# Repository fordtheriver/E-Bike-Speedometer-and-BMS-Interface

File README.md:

# E-Bike-Speedometer-and-BMS-Interface

**Updated 7/25/19** Completed, manufactured, and test REV4 of board. It works! REV3 is also complete.

This repository includes information needed to built a display to output the speed, mileage, power, current, pack voltage, individual cell voltage abd State of Charge of an electric bicycle/powerwall using an Arduino Nano! This repository includes the necessary Arduino files, a custom Arduino shield PCB designed in EAGLE and various information about the components required to build this system.

There are two versions of this system which you can build: <br /> 
**REV3:** This is a simple board that requires little soldering or PCB design experience. Beginners start here! <br /> 
**REV4:** This board is identical to REV3 but it embedds the arduino nano onto the board, instead of through-hole mounting a off-the-shelf arduino nano. <br /> 
Both REV's function identically. Think of REV3 as a demo board where you can develop firmware and prototype the system. REV4 gets into the low level side and allows for greater custimizations and smaller size.

Here is a brief list describing the necessary high level components for this system.

1. Arduino Nano. REV4 embeds the ATmega328P micrcoprocessor on the board to significantly reduce system size and weight. 

2. [20x4 LCD Display with I2C.](https://www.ebay.com/sch/i.html?_from=R40&_trksid=m570.l1313&_nkw=20x4+i2c+lcd+&_sacat=0). The I2C communication bus drastically reduces the number of wires going to the LCD and the \#include <LiquidCrystal_I2C.h> library seamlessly integrates the I2C protocol into your arduino. 

3. JBDTools Compatible BMS: Here is a [link](https://www.aliexpress.com/item/15S-Li-ion-Battery-Intelligent-Smart-BMS-with-Bluetooth-function-and-PC-software-UART-communication-PCB/32876909159.html?spm=a2g0s.13010208.99999999.263.70483c00UKdgf7) to the one I purchased.  . Make sure the BMS you buy is compatible with JBDTools software. My arduino script uses the communication protocol used by the JBDTools software. This protocol can be found in an excel file call JBDTools Communication Protol at the homepage of this repository. [Simat](https://github.com/simat/BatteryMonitor/wiki/Generic-Chinese-Bluetooth-BMS-communication-protocol) also has a great description of it as well. 

4. DC/DC Converter. The linear voltage regulator on [this](https://www.aliexpress.com/item/15S-Li-ion-Battery-Intelligent-Smart-BMS-with-Bluetooth-function-and-PC-software-UART-communication-PCB/32876909159.html?spm=a2g0s.13010208.99999999.263.70483c00UKdgf7) type of BMS is not designed to handle high amounts of current. REV3 of this project includes [this](https://www.mouser.com/ProductDetail/MEAN-WELL/SKM15C-12?qs=erfQA2AIGbWiXI5iTXq5SA%3D%3D) or [this](https://www.mouser.com/ProductDetail/Cincon/EC4SBW-48S12?qs=sGAEpiMZZMvGsmoEFRKS8Koqt8Pjkl39iYdgR2DcyS1Q8fqJi%252BFKOA%3D%3D) DC/DC converter to provide 12V at a max of 1.25A to the system.

5. [Hall effect sensor.](https://www.adafruit.com/product/158). This type of sensor send a HIGH pulse whenever a significant magnetic field acts upon it.

6. Connectors. [Housing](https://www.mouser.com/ProductDetail/Molex/70543-0001?qs=sGAEpiMZZMtVoztFdqDXOwZ%252B3K3gi96X). [Plug](https://www.mouser.com/ProductDetail/Molex/50-57-9402?qs=%2Fha2pyFaduiLH0020kLaRTyvVPMd9o3wI7LfZqK7vYk%3D). [Crimp Pin](https://www.mouser.com/ProductDetail/Molex/16-02-0086-Cut-Strip?qs=sGAEpiMZZMs%252BGHln7q6pm%252Bv5BXf4QdrTI%252BpAylNNmmH%2F60rOt1UzkQ%3D%3D)

7. EAGLE PCB design software. I used [OSHPark](https://oshpark.com/) to manufacture the PCB and had no issues. 

# High Level System Requirements:

1. Input Voltage Range: 18 - 72 Volts
2. Max Power Output at 12V: 1.67 Amps (20W)
3. Reverse polarity and fuse protection on power input

# Good Tips:

My ebike uses the Cyclone 3000 ebike kit. The throttle/ignition has a built in switch on the B+ line. My system draws power from the B+ after this switch so that if the switch opens, the system turns off. I recommend configuring your system this way so that it only draws power when the bike is on.

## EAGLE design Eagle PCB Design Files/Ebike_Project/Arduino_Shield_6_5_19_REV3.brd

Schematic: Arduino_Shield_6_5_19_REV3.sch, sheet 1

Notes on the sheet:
Connector Housing Series 70543 - Part No: 705430004 (4 PIN)
Connector Plug Series 70066 - Part No: 505794XX
Connector Crimp Series 70058 - Part No: 16020086
Wire to Wire Housing Crimp: 70021-1021
Wire to Wire Housing Series: 70107 - Part No: 701070003
BMS_SWITCH
IGNITION_SWITCH

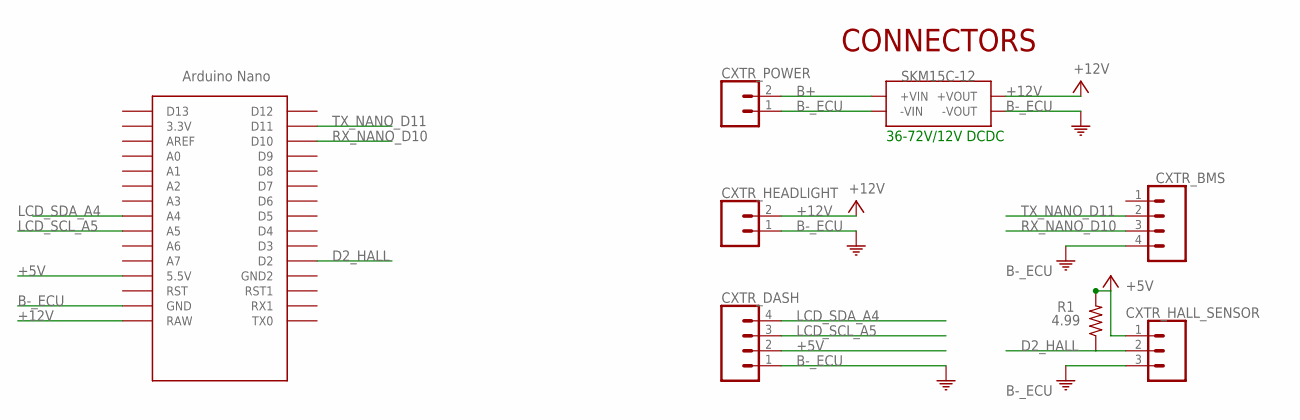
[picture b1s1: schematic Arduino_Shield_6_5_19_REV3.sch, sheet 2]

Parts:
CXTR_BMS: 4PIN_.1"_CONNECTOR; 1X04
CXTR_DASH: 4PIN_.1"_CONNECTOR; 1X04
CXTR_HALL_SENSOR: 3PIN_.1"_CONNECTOR; 1X03
CXTR_HEADLIGHT: 2PIN_.1"_CONNECTOR; 1X02
CXTR_POWER: 2PIN_.1"_CONNECTOR; 1X02
R1: 4.99; 0805
U$2: SKM15C-12_DCDC
U$3: ARDUINO_NANO; NANO

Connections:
+5V: CXTR_DASH.2, CXTR_HALL_SENSOR.1, R1.2, U$3.5V (5.5V)
+12V: CXTR_HEADLIGHT.2, U$2.+VOUT, U$3.RAW
B+: CXTR_POWER.2, U$2.+VIN
B-_ECU: CXTR_BMS.4, CXTR_DASH.1, CXTR_HALL_SENSOR.3, CXTR_HEADLIGHT.1, CXTR_POWER.1, U$2.-VIN, U$2.-VOUT, U$3.GND
D2_HALL: CXTR_HALL_SENSOR.2, R1.1, U$3.D2
LCD_SCL_A5: CXTR_DASH.3, U$3.A5
LCD_SDA_A4: CXTR_DASH.4, U$3.A4
RX_NANO_D10: CXTR_BMS.3, U$3.D10
TX_NANO_D11: CXTR_BMS.2, U$3.D11

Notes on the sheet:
36-72V/12V DCDC
CONNECTORS

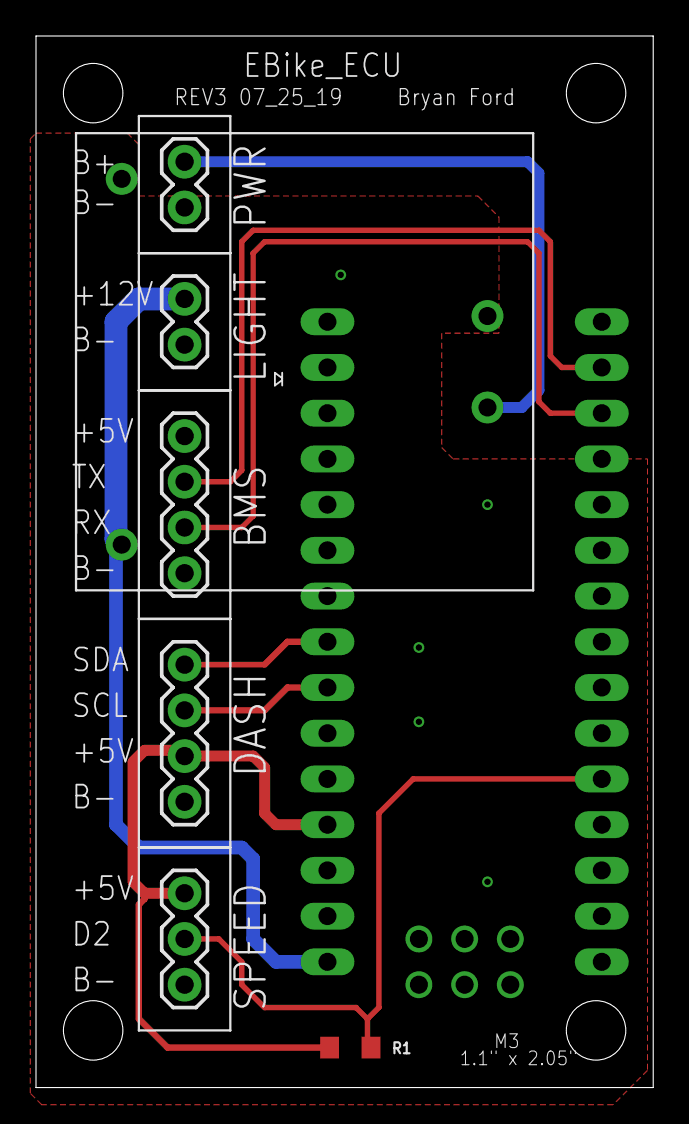
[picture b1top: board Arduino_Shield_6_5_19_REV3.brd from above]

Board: 2 copper layers, 34.3 x 58.4 mm, 8 parts (0 on the bottom side), 9 nets.

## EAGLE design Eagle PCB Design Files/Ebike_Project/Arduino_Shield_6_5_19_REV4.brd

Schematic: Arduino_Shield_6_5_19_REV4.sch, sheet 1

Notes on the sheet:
Connector Housing Series 70543 - Part No: 705430004 (4 PIN)
Connector Plug Series 70066 - Part No: 505794XX
Connector Crimp Series 70058 - Part No: 16020086
Wire to Wire Housing Crimp: 70021-1021
Wire to Wire Housing Series: 70107 - Part No: 701070003
BMS_SWITCH
IGNITION_SWITCH

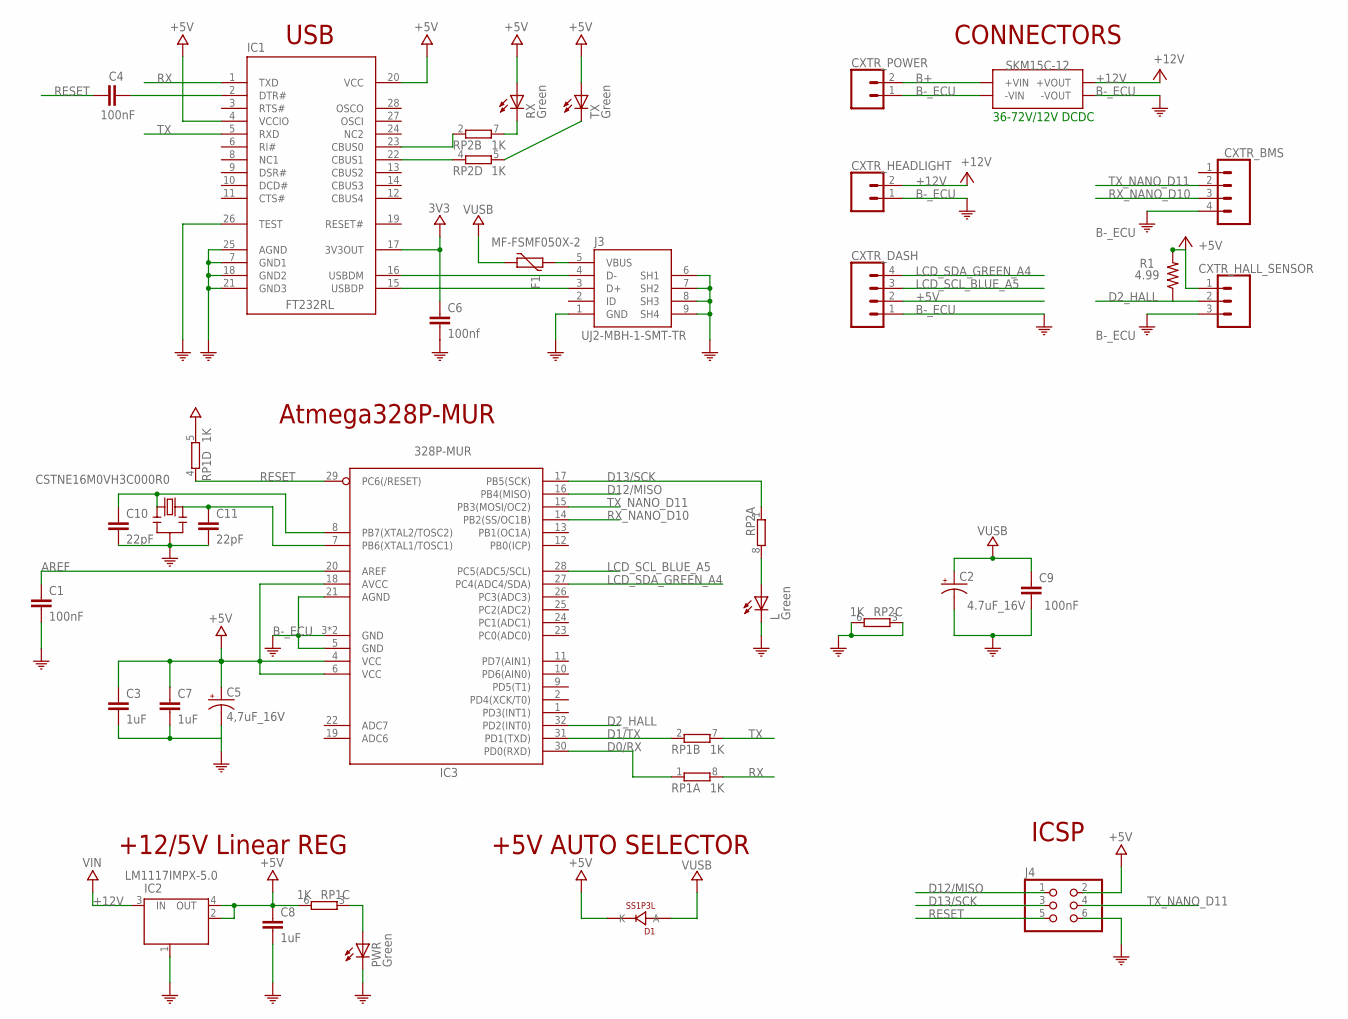
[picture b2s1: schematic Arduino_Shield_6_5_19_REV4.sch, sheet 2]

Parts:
C1, C4, C9: 100nF; 0805
C2: 4.7uF_16V; 0805
C3, C7, C8: 1uF; 0805
C5: 4,7uF_16V; 0805
C6: 100nf; 0805
C10, C11: 22pF; 0805
CXTR_BMS: 4PIN_.1"_CONNECTOR; 1X04
CXTR_DASH: 4PIN_.1"_CONNECTOR; 1X04
CXTR_HALL_SENSOR: 3PIN_.1"_CONNECTOR; 1X03
CXTR_HEADLIGHT: 2PIN_.1"_CONNECTOR; 1X02
CXTR_POWER: 2PIN_.1"_CONNECTOR; 1X02
D1: SS1P3L; SCHOTTKY_DIODE_DO220AAL
F1: MF-FSMF050X-2; 0603
IC1: FT232RL; USB_SSOP28
IC2: LM1117IMPX-5.0; LINEAR_VREG_SOT223
IC3: 328P-MUR; VQFN32
J3: UJ2-MBH-1-SMT-TR; USB-MINI-B_2
J4: 2X3_.1"_ARRAY; 2X03
L: Green; LED_0805
PWR: Green; LED_0805
R1: 4.99; 0805
RESONATOR: CSTNE16M0VH3C000R0; CRISTALLI_RESONATOR
RP1, RP2: 1K; RESISTOR_ARRAY_CAY16
RX: Green; LED_0805
TX: Green; LED_0805
U$2: SKM15C-12_DCDC

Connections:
3V3: C6.1, IC1.17 (3V3OUT)
+5V: C3.1, C5.1 (+), C7.1, C8.1, CXTR_DASH.2, CXTR_HALL_SENSOR.1, D1.P$1 (K), IC1.4 (VCCIO), IC1.20 (VCC), IC2.2 (OUT), IC2.4 (OUT), IC3.4 (VCC), IC3.6 (VCC), IC3.18 (AVCC), J4.2, R1.2, RP1.5 (2), RP1.6 (2), RX.A, TX.A
+12V: CXTR_HEADLIGHT.2, IC2.3 (IN), U$2.+VOUT
AREF: C1.1, IC3.20 (AREF)
B+: CXTR_POWER.2, U$2.+VIN
B-_ECU: C1.2, C2.2 (-), C3.2, C5.2 (-), C6.2, C7.2, C8.2, C9.2, C10.2, C11.2, CXTR_BMS.4, CXTR_DASH.1, CXTR_HALL_SENSOR.3, CXTR_HEADLIGHT.1, CXTR_POWER.1, IC1.7 (GND1), IC1.18 (GND2), IC1.21 (GND3), IC1.25 (AGND), IC1.26 (TEST), IC2.1 (GND/ADJ), IC3.3 (GND), IC3.5 (GND), IC3.21 (AGND), IC3.33 (GND), J3.1 (GND), J3.6 (SH1), J3.7 (SH2), J3.8 (SH3), J3.9 (SH4), J4.6, L.C, PWR.C, RESONATOR.2, RP2.3 (1), RP2.6 (2), U$2.-VIN, U$2.-VOUT
D0/RX: IC3.30 (PD0(RXD)), RP1.1
D1/TX: IC3.31 (PD1(TXD)), RP1.2 (1)
D2_HALL: CXTR_HALL_SENSOR.2, IC3.32 (PD2(INT0)), R1.1
D12/MISO: IC3.16 (PB4(MISO)), J4.1
D13/SCK: IC3.17 (PB5(SCK)), J4.3, RP2.1
LCD_SCL_BLUE_A5: CXTR_DASH.3, IC3.28 (PC5(ADC5/SCL))
LCD_SDA_GREEN_A4: CXTR_DASH.4, IC3.27 (PC4(ADC4/SDA))
unnamed: C4.2, IC1.2 (DTR#)
unnamed: IC1.15 (USBDP), J3.3 (D+)
unnamed: IC1.16 (USBDM), J3.4 (D-)
unnamed: PWR.A, RP1.3 (1)
unnamed: IC1.23 (CBUS0), RP2.2 (1)
unnamed: IC1.22 (CBUS1), RP2.4 (1)
unnamed: C11.1, IC3.7 (PB6(XTAL1/TOSC1)), RESONATOR.1
unnamed: L.A, RP2.8 (2)
unnamed: RP2.5 (2), TX.C
unnamed: C10.1, IC3.8 (PB7(XTAL2/TOSC2)), RESONATOR.3
unnamed: F1.2, J3.5 (VBUS)
unnamed: RP2.7 (2), RX.C
RESET: C4.1, IC3.29 (PC6(/RESET)), J4.5, RP1.4 (1)
RX: IC1.1 (TXD), RP1.8 (2)
RX_NANO_D10: CXTR_BMS.3, IC3.14 (PB2(SS/OC1B))
TX: IC1.5 (RXD), RP1.7 (2)
TX_NANO_D11: CXTR_BMS.2, IC3.15 (PB3(MOSI/OC2)), J4.4
VUSB: C2.1 (+), C9.1, D1.P$2 (A), F1.1

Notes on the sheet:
+12/5V Linear REG
ICSP
USB
+5V AUTO SELECTOR
36-72V/12V DCDC
Atmega328P-MUR
CONNECTORS

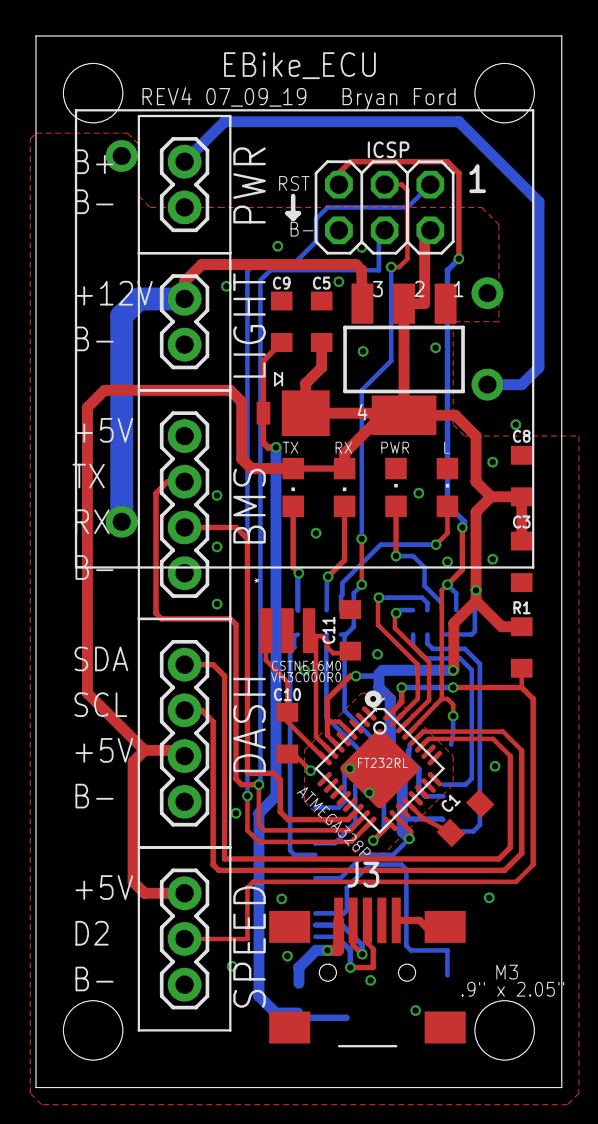
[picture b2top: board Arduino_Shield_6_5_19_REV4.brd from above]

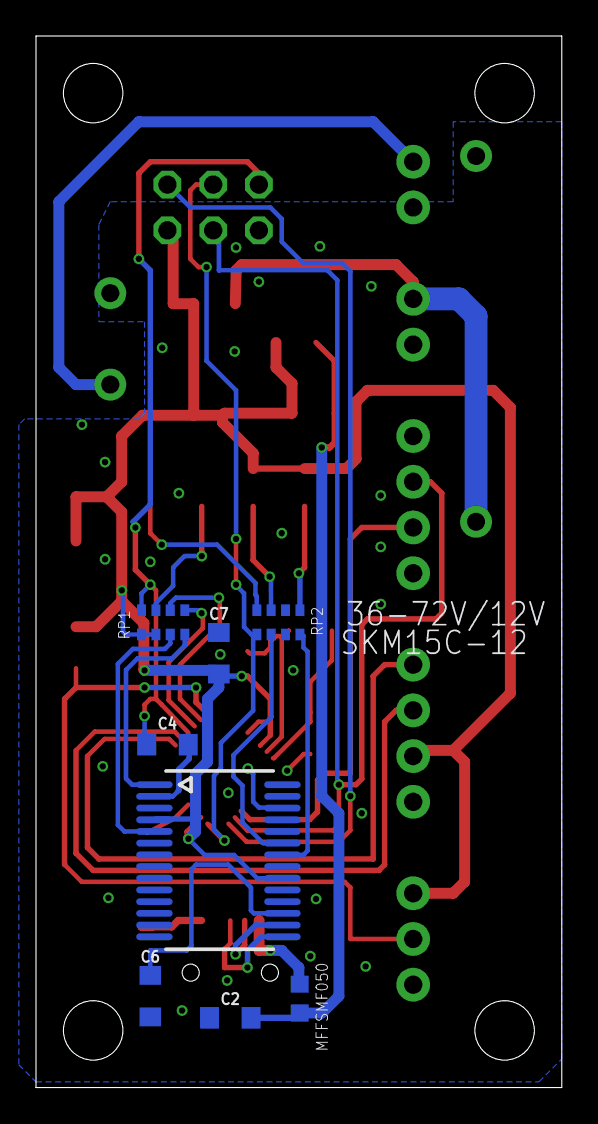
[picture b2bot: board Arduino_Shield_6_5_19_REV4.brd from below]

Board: 2 copper layers, 29.2 x 58.4 mm, 32 parts (8 on the bottom side), 31 nets.

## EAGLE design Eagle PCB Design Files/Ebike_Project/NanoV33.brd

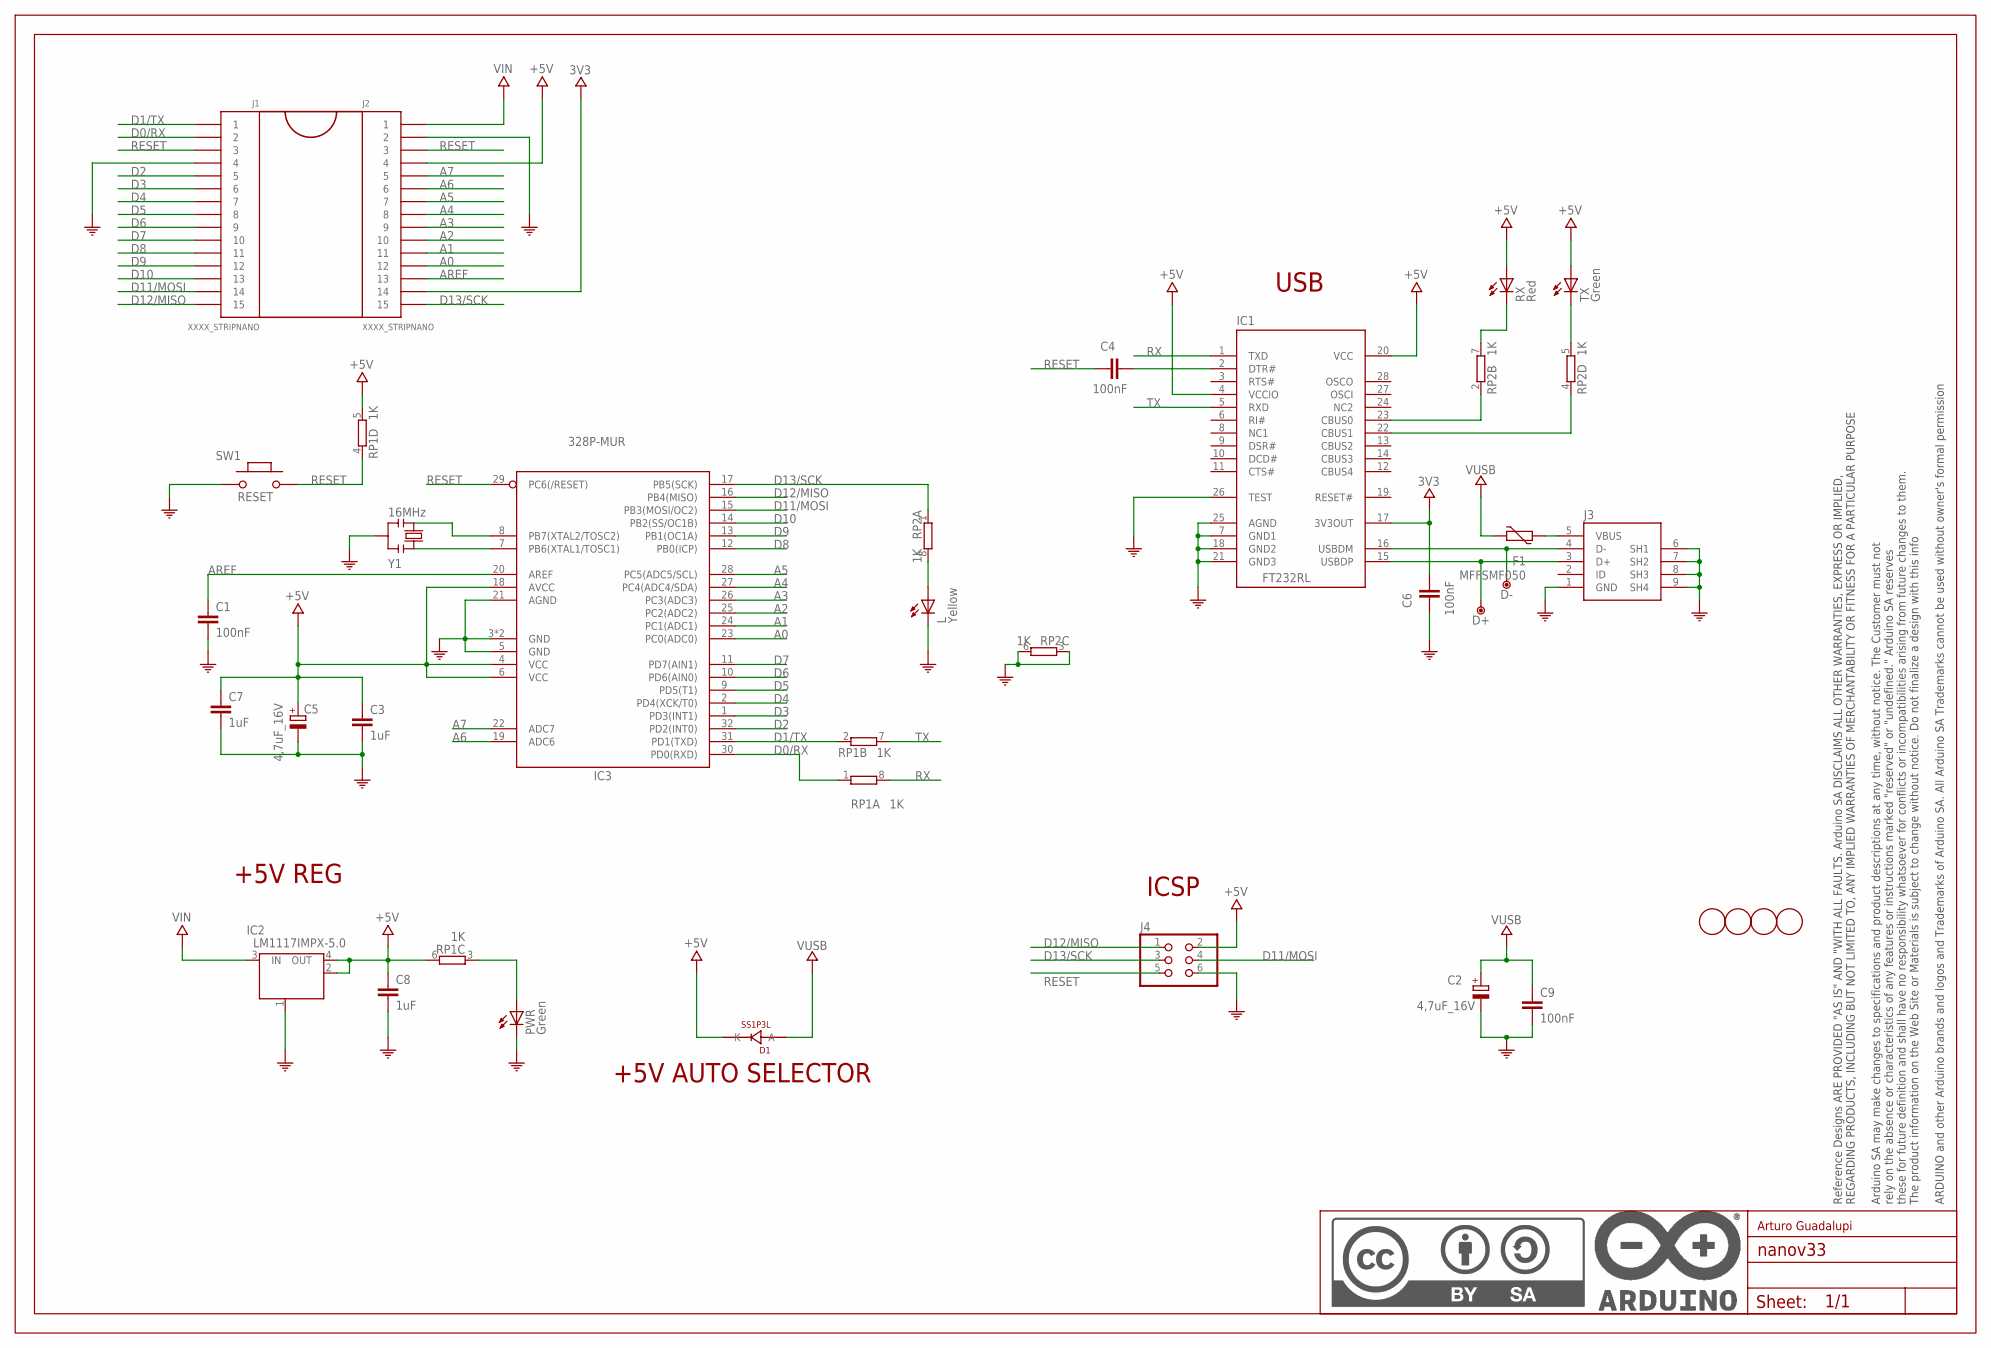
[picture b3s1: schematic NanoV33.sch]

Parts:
C1, C4, C6, C9: 100nF; C0603-ROUND
C2, C5: 4,7uF_16V; TAN-A
C3, C7, C8: 1uF; C0603-ROUND
D1: SS1P3L; DO220AAL
D+: DNP; TP-1.00MM
D-: DNP; TP-1.00MM
F1: MFFSMF050; 0603-1608X90N
FRAME1: DNP; FRAME
IC1: FT232RL; SSOP28
IC2: LM1117IMPX-5.0; LINEAR_SOT223
IC3: 328P-MUR; VQFN32
J1, J2: XXXX_STRIPNANO; HEAD15-NOSS
J3: 0219_14850; USB-MINI-B_2
J4: 0114_PH254-203DF118A00V; 2X03
L: Yellow; CHIPLED_0805
PWR: Green; CHIPLED_0805
RP1, RP2: 1K; CAY16
RX: Red; CHIPLED_0805
SW1: RESET; SMD_157SW
TX: Green; CHIPLED_0805
U$4, U$5, U$53, U$54: DNP; FD-1-1.5
Y1: 16MHz; RESONATOR

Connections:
3V3: C6.2, IC1.17 (3V3OUT), J2.14
+5V: C3.1, C5.1 (+), C7.1, C8.1, D1.P$1 (K), IC1.4 (VCCIO), IC1.20 (VCC), IC2.2 (OUT), IC2.4 (OUT), IC3.4 (VCC), IC3.6 (VCC), IC3.18 (AVCC), J2.4, J4.2, RP1.5 (2), RP1.6 (2), RX.A, TX.A
A0: IC3.23 (PC0(ADC0)), J2.12
A1: IC3.24 (PC1(ADC1)), J2.11
A2: IC3.25 (PC2(ADC2)), J2.10
A3: IC3.26 (PC3(ADC3)), J2.9
A4: IC3.27 (PC4(ADC4/SDA)), J2.8
A5: IC3.28 (PC5(ADC5/SCL)), J2.7
A6: IC3.19 (ADC6), J2.6
A7: IC3.22 (ADC7), J2.5
AREF: C1.1, IC3.20 (AREF), J2.13
COM: C1.2, C2.2 (-), C3.2, C5.2 (-), C6.1, C7.2, C8.2, C9.2, IC1.7 (GND1), IC1.18 (GND2), IC1.21 (GND3), IC1.25 (AGND), IC1.26 (TEST), IC2.1 (GND/ADJ), IC3.3 (GND), IC3.5 (GND), IC3.21 (AGND), IC3.33 (GND), J1.4, J2.2, J3.1 (GND), J3.6 (SH1), J3.7 (SH2), J3.8 (SH3), J3.9 (SH4), J4.6, L.C, PWR.C, RP2.3 (1), RP2.6 (2), SW1.1, Y1.2
D0/RX: IC3.30 (PD0(RXD)), J1.2, RP1.1
D1/TX: IC3.31 (PD1(TXD)), J1.1, RP1.2 (1)
D2: IC3.32 (PD2(INT0)), J1.5
D3: IC3.1 (PD3(INT1)), J1.6
D4: IC3.2 (PD4(XCK/T0)), J1.7
D5: IC3.9 (PD5(T1)), J1.8
D6: IC3.10 (PD6(AIN0)), J1.9
D7: IC3.11 (PD7(AIN1)), J1.10
D8: IC3.12 (PB0(ICP)), J1.11
D9: IC3.13 (PB1(OC1A)), J1.12
D10: IC3.14 (PB2(SS/OC1B)), J1.13
D11/MOSI: IC3.15 (PB3(MOSI/OC2)), J1.14, J4.4
D12/MISO: IC3.16 (PB4(MISO)), J1.15, J4.1
D13/SCK: IC3.17 (PB5(SCK)), J2.15, J4.3, RP2.1
unnamed: IC3.8 (PB7(XTAL2/TOSC2)), Y1.3
unnamed: IC3.7 (PB6(XTAL1/TOSC1)), Y1.1
unnamed: PWR.A, RP1.3 (1)
unnamed: C4.2, IC1.2 (DTR#)
unnamed: D+.X, IC1.15 (USBDP), J3.3 (D+)
unnamed: D-.X, IC1.16 (USBDM), J3.4 (D-)
unnamed: L.A, RP2.8 (2)
unnamed: IC1.23 (CBUS0), RP2.2 (1)
unnamed: IC1.22 (CBUS1), RP2.4 (1)
unnamed: RP2.5 (2), TX.C
unnamed: F1.2, J3.5 (VBUS)
unnamed: RP2.7 (2), RX.C
RESET: C4.1, IC3.29 (PC6(/RESET)), J1.3, J2.3, J4.5, RP1.4 (1), SW1.2
RX: IC1.1 (TXD), RP1.8 (2)
TX: IC1.5 (RXD), RP1.7 (2)
VIN: IC2.3 (IN), J2.1
VUSB: C2.1 (+), C9.1, D1.P$2 (A), F1.1

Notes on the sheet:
+5V REG
ICSP
USB
+5V AUTO SELECTOR
Arturo Guadalupi

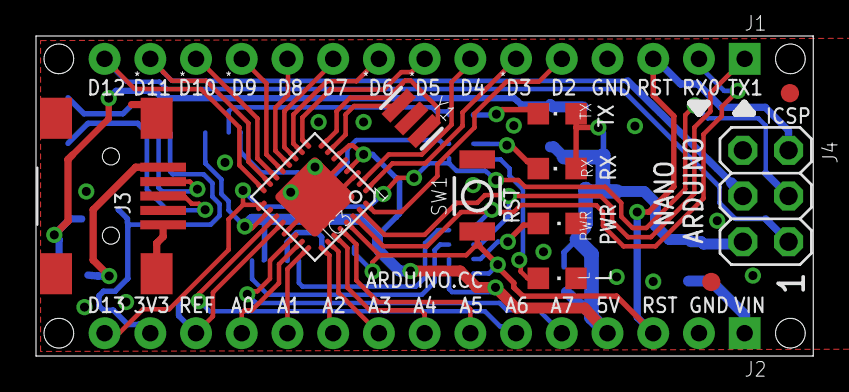
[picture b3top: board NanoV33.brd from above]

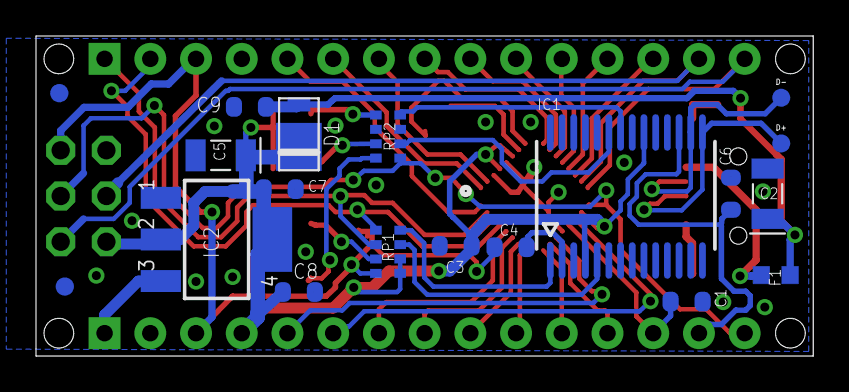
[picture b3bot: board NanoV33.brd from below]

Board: 2 copper layers, 43.2 x 17.8 mm, 33 parts (17 on the bottom side), 43 nets.

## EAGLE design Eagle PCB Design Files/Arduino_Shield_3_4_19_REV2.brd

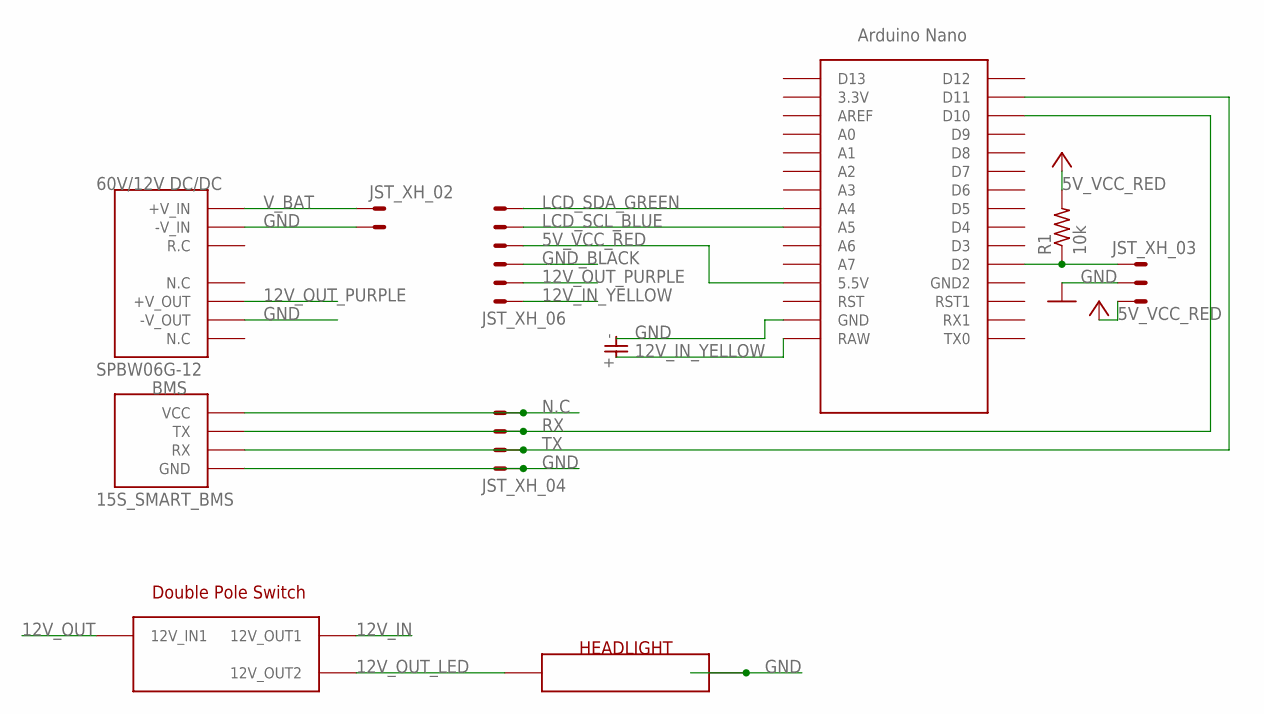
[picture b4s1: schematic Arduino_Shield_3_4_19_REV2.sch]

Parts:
R1: 10k; R0805
U$1: NANO
U$2: SPBW06G-12
U$3: THROUGHHOLE_CAP
X1: JST_XH_04; JST-XH-04-PACKAGE-LONG-PAD
X2: JST_XH_06; JST-XH-06-PACKAGE-LONG-PAD
X4: JST_XH_02; JST-XH-02-PACKAGE-LONG-PAD
X5: JST_XH_03; JST-XH-03-PACKAGE-LONG-PAD

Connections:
5V_VCC_RED: R1.2, U$1.5V (5.5V), X2.4, X5.3
12V_IN_YELLOW: U$1.RAW, U$3.+, X2.1
12V_OUT_PURPLE: U$2.+V_OUT, X2.2
GND: U$1.GND, U$2.-V_IN, U$2.-V_OUT, U$3.-, X1.1, X4.2, X5.2
GND_BLACK: X2.3
LCD_SCL_BLUE: U$1.A5, X2.5
LCD_SDA_GREEN: U$1.A4, X2.6
unnamed: R1.1, U$1.D2, X5.1
N.C: X1.4
RX: U$1.D10, X1.3
TX: U$1.D11, X1.2
V_BAT: U$2.+V_IN, X4.1

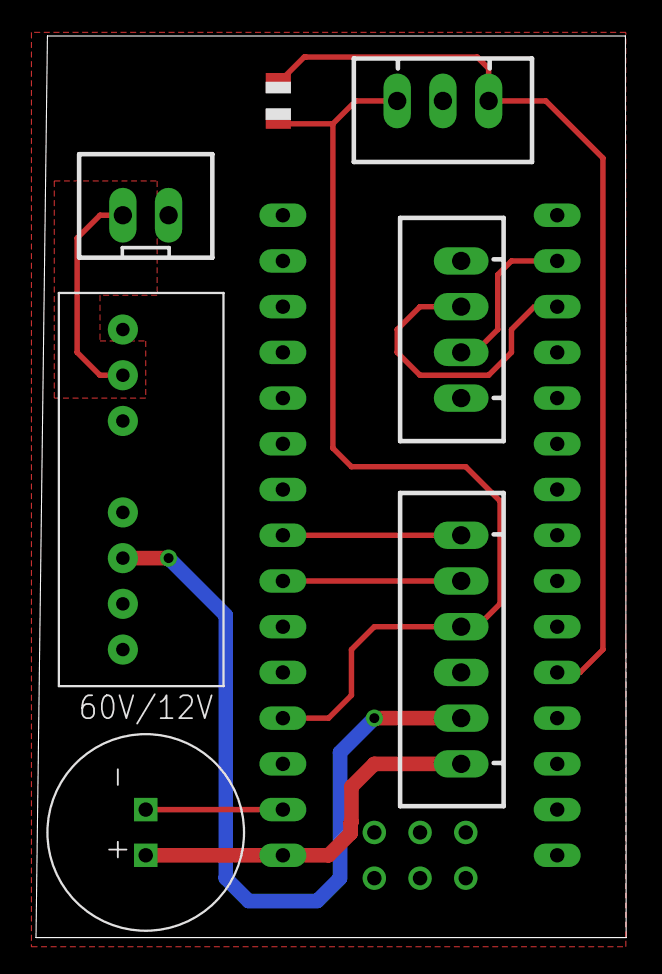
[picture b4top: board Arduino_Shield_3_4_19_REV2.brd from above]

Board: 2 copper layers, 32.8 x 50.1 mm, 8 parts (0 on the bottom side), 10 nets.

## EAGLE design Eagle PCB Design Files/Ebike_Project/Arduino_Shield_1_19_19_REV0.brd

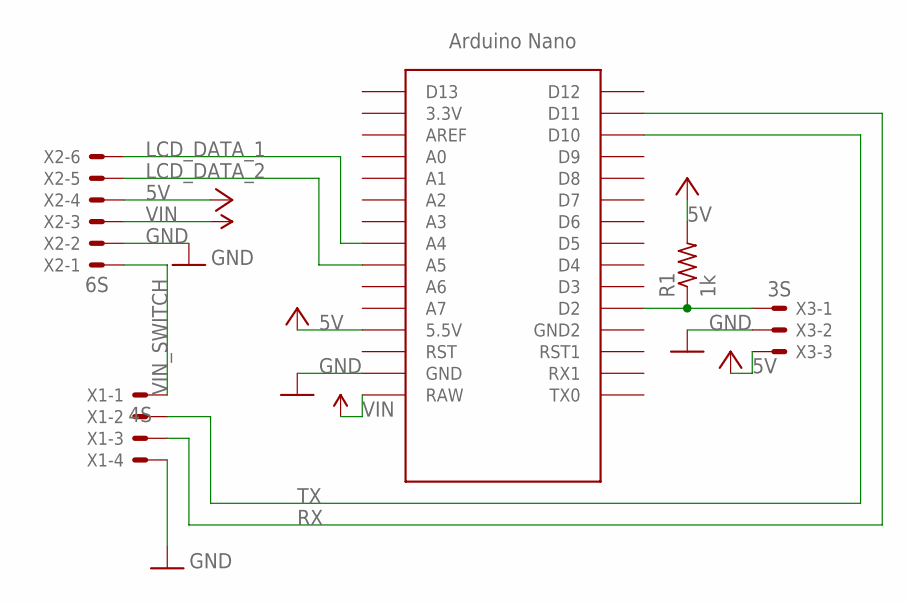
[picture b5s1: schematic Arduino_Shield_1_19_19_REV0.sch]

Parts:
R1: 1k; R0805
U$1: NANO
X1: 4S; JST-XH-04-PACKAGE-ROUND-PAD
X2: 6S; JST-XH-06-PACKAGE-ROUND-PAD
X3: 3S; JST-XH-03-PACKAGE-ROUND-PAD

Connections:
5V: R1.2, U$1.5V (5.5V), X2.4, X3.3
GND: U$1.GND, X1.4, X2.2, X3.2
LCD_DATA_1: U$1.A4, X2.6
LCD_DATA_2: U$1.A5, X2.5
unnamed: R1.1, U$1.D2, X3.1
RX: U$1.D11, X1.3
TX: U$1.D10, X1.2
VIN: U$1.RAW, X2.3
VIN_SWITCH: X1.1, X2.1

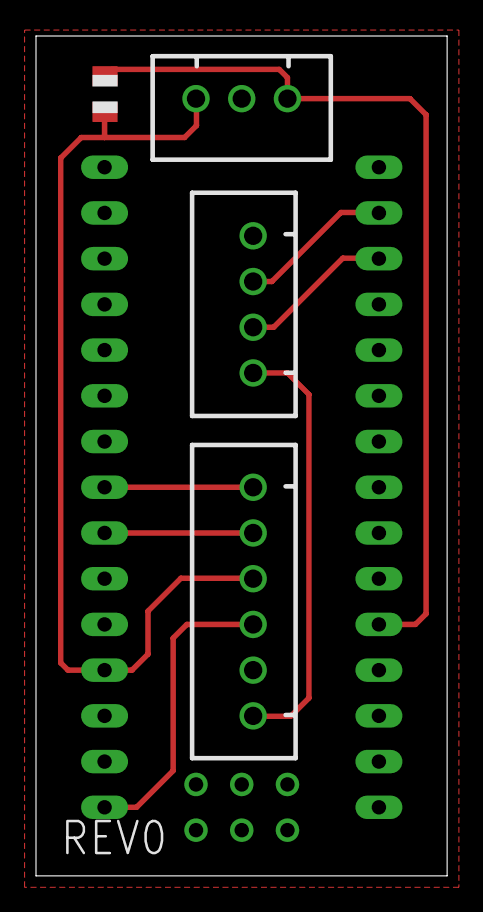
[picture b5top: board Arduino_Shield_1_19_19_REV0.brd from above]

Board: 2 copper layers, 22.8 x 46.7 mm, 5 parts (0 on the bottom side), 9 nets.

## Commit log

2019-02-09 Added Folders to organize files
2019-02-10 Added BETA version of Arduino software
2019-02-10 Created README
2019-02-23 Project Pictures
2019-04-02 Added updated EAGLE Files
    Includes DC/DC converter, capacitor, and better labeling silkscreens
2019-06-06 Updated High Level Design
    Refurbishing schematic dseign for clarity
2019-06-19 Updated Read Me to include system requirements
2019-06-21 Completed REV3 of board
    REV adds a larger DC/DC converter and connector for a 12V headlight
2019-07-08 Completed REV4
2019-07-11 REV4 is Complete, PCB and BOM sent out
    Evaluation of REV4 will be completed by the end of July
2019-07-25 Corrected polarity of DCDC converter of REV4 board
2019-07-26 Completed REV3
    REV3 is identical to REV4 but uses an off the shelf arduino nano.
2019-07-28 Updated REV4 to include fuse & input polarity protection

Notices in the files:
parts and their libraries:
SparkFun-PowerSymbols: Licensing: Creative Commons ShareAlike 4.0 International - https://creativecommons.org/licenses/by-sa/4.0
Arduino-utility: Copyright (c) 2016-2017 Arduino LLC.  All right reserved.
